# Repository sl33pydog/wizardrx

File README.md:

# STOP!
__This project was forked from github but the code is from GitLab:__ https://gitlab.com/PropNuts/wizardrx

This code has been re configured to be used on a esp32 Wroom uploaded via arduino ide.  The purpose of this fork is to present a path to incorporate into the clearview_interface_public __ https://github.com/ryaniftron/clearview_interface_public to then be used as a mirrored node for video streaming via MQTT commands for RotorHazard __ https://github.com/RotorHazard/RotorHazard  The set frequency command needs to be changed from a set frequency to actual commands via MQTT.

The other option instead of using a 4 digit freqency number would be to use a matrix of channel numbers and frequency groups that every typically uses.  This is where I probably would need help and or the use of another project that has already do this.

This is my first attempt at code so it may be ineffecient.  My only changes were to the .ino main file.  The Reciever and RecieverSPIDriver code are exact copies of Propnuts WizardRX firmware found at their github site.

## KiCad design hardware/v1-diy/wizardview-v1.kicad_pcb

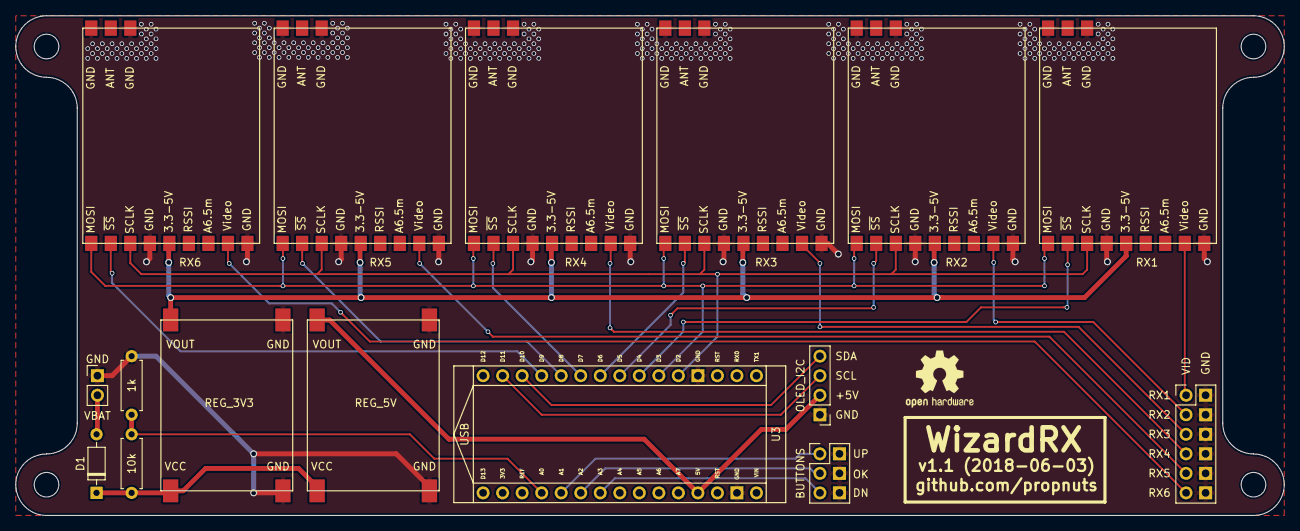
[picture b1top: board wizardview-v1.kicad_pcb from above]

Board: 2 copper layers, 165.0 x 65.0 mm, 16 parts (0 on the bottom side), 25 nets.

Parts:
D1: D; D_DO-35_SOD27_P7.62mm_Horizontal
J1: POWER_IN; PinHeader_1x02_P2.54mm_Vertical
J2: VID_OUT; PinHeader_2x06_P2.54mm_Vertical
J3: BUTTONS; PinHeader_2x03_P2.54mm_Vertical
OLED1: OLED_I2C; PinHeader_1x04_P2.54mm_Vertical
R1: 10k; R_Axial_DIN0207_L6.3mm_D2.5mm_P7.62mm_Horizontal
R2: 1k; R_Axial_DIN0207_L6.3mm_D2.5mm_P7.62mm_Horizontal
RX1, RX2, RX3, RX4, RX5, RX6: RX5808
U1: REG_5V; BG_REG
U2: REG_3V3; BG_REG
U3: ArduinoNano

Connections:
+3V3: RX1.5, RX2.5, RX3.5, RX4.5, RX5.5, RX6.5, U2.4
+5V: OLED1.2, U1.4, U3.19
/BTN_DN: J3.5, U3.24
/BTN_OK: J3.3, U3.25
/BTN_UP: J3.1, U3.26
/MOSI: RX1.9, RX2.9, RX3.9, RX4.9, RX5.9, RX6.9, U3.6
/SCL: OLED1.3, U3.14
/SCLK: RX1.7, RX2.7, RX3.7, RX4.7, RX5.7, RX6.7, U3.5
/SDA: OLED1.4, U3.13
/SS_RX1: RX1.8, U3.7
/SS_RX2: RX2.8, U3.8
/SS_RX3: RX3.8, U3.9
/SS_RX4: RX4.8, U3.10
/SS_RX5: RX5.8, U3.11
/SS_RX6: RX6.8, U3.12
/VCC_SENSE: R1.1, R2.2, U3.27
/VID1: J2.1, RX1.2
/VID2: J2.3, RX2.2
/VID3: J2.5, RX3.2
/VID4: J2.7, RX4.2
/VID5: J2.9, RX5.2
/VID6: J2.11, RX6.2
GND: J1.1, J2.2, J2.4, J2.6, J2.8, J2.10, J2.12, J3.2, J3.4, J3.6, OLED1.1, R2.1, RX1.1, RX1.6, RX1.10, RX1.12, RX2.1, RX2.6, RX2.10, RX2.12, RX3.1, RX3.6, RX3.10, RX3.12, RX4.1, RX4.6, RX4.10, RX4.12, RX5.1, RX5.6, RX5.10, RX5.12, RX6.1, RX6.6, RX6.10, RX6.12, U1.1, U1.3, U2.1, U2.3, U3.4, U3.17
unnamed: D1.2, J1.2
VCC: D1.1, R1.2, U1.2, U2.2

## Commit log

2018-06-03 First commit.
2020-08-02 Create Code
2020-08-02 Create About
2020-08-02 Rename Wizard_CV_RX_Node.ino to Source/Wizard_CV_RX_Node.ino
2020-08-02 Rename Receiver.cpp to Source/Receiver.cpp
2020-08-02 Rename Receiver.h to Source/Receiver.h
2020-08-02 Rename ReceiverSpiDriver.cpp to Source/ReceiverSpiDriver.cpp
2020-08-02 Rename ReceiverSpiDriver.h to Source/ReceiverSpiDriver.h
2020-08-02 Rename About to About.md
